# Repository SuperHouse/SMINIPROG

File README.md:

Sonoff Mini Programming Jig
===========================
Copyright 2019-2020 SuperHouse Automation Pty Ltd  www.superhouse.tv  

Pogo pin board for programming a Sonoff Mini using the test points on
its PCB.

Exposes the connections to an ESP-Prog header, which can be used for
discrete wire connections or to plug in an ESPFlasher programmer.

www.superhouse.tv/sminiprog

INSTALLATION
------------
The design is saved as an EAGLE project. EAGLE PCB design software is
available from www.cadsoftusa.com free for non-commercial use. To use
this project download it and place the directory containing these files
into the "eagle" directory on your computer. Then open EAGLE and
navigate to the project.

DISTRIBUTION
------------
The specific terms of distribution of this project are governed by the
license referenced below.

LICENSE
-------
Licensed under the TAPR Open Hardware License (www.tapr.org/OHL).
The "license" folder within this repository also contains a copy of
this license in plain text format.

CREDITS
-------
Designed by Jonathan Oxer (jon@oxer.com.au)

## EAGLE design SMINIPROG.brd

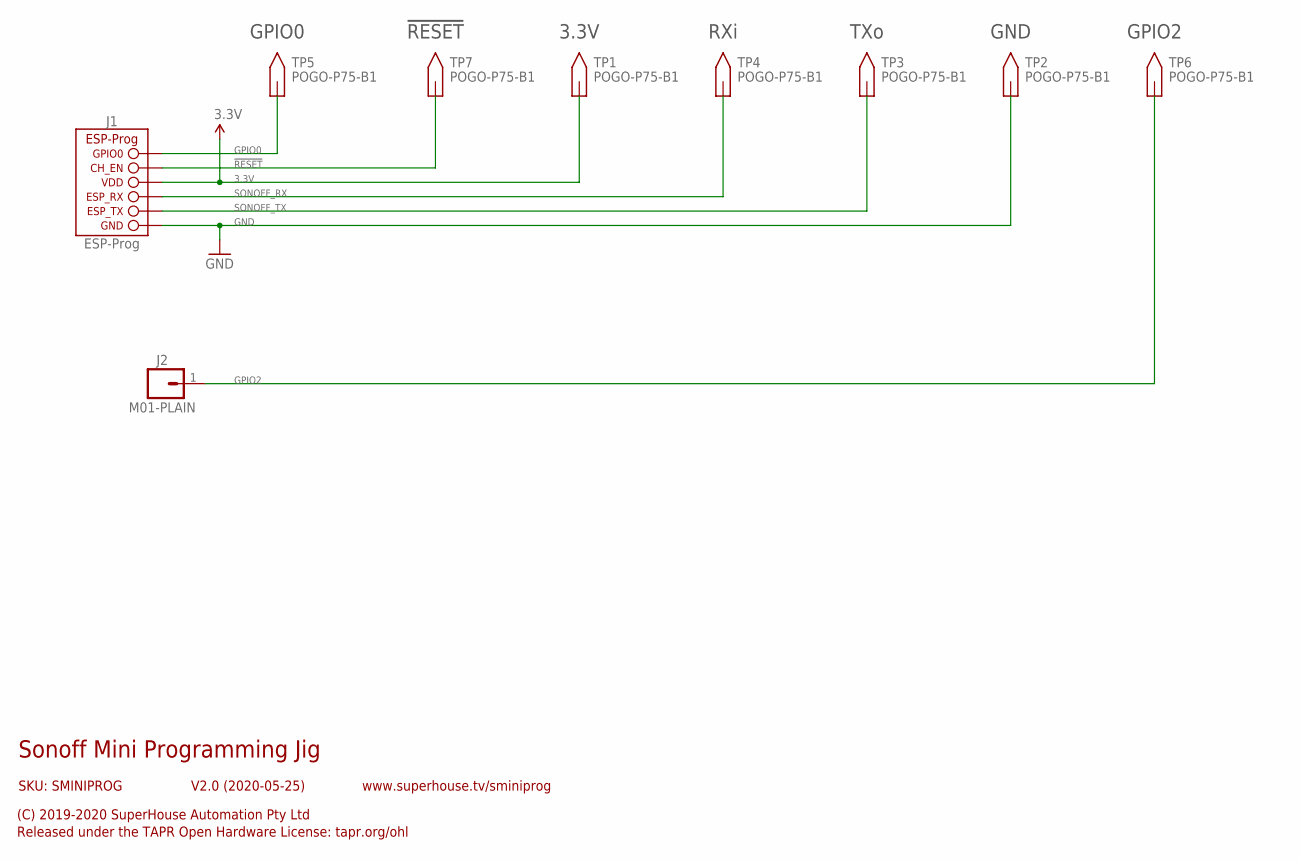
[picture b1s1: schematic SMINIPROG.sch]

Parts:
J1: ESP-PROG-1X6-2.54-SOCKET-RA; 1X6-2.54-SOCKET-RA
J2: M01-PLAIN; 1X01
TP1, TP2, TP3, TP4, TP5, TP6, TP7: POGO-P75-B1; PIN-1.02

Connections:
3.3V: J1.4 (VDD), TP1.P$1
!RESET: J1.5 (CH_EN), TP7.P$1
GND: J1.1 (GND), TP2.P$1
GPIO0: J1.6 (GPIO0), TP5.P$1
GPIO2: J2.1, TP6.P$1
SONOFF_RX: J1.3 (ESP_RX), TP4.P$1
SONOFF_TX: J1.2 (ESP_TX), TP3.P$1

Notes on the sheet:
Sonoff Mini Programming Jig
V2.0 (2020-05-25)
(C) 2019-2020 SuperHouse Automation Pty Ltd
Released under the TAPR Open Hardware License: tapr.org/ohl
www.superhouse.tv/sminiprog
SKU: SMINIPROG
3.3V
GND
TXo
RXi
GPIO0
GPIO2
!RESET

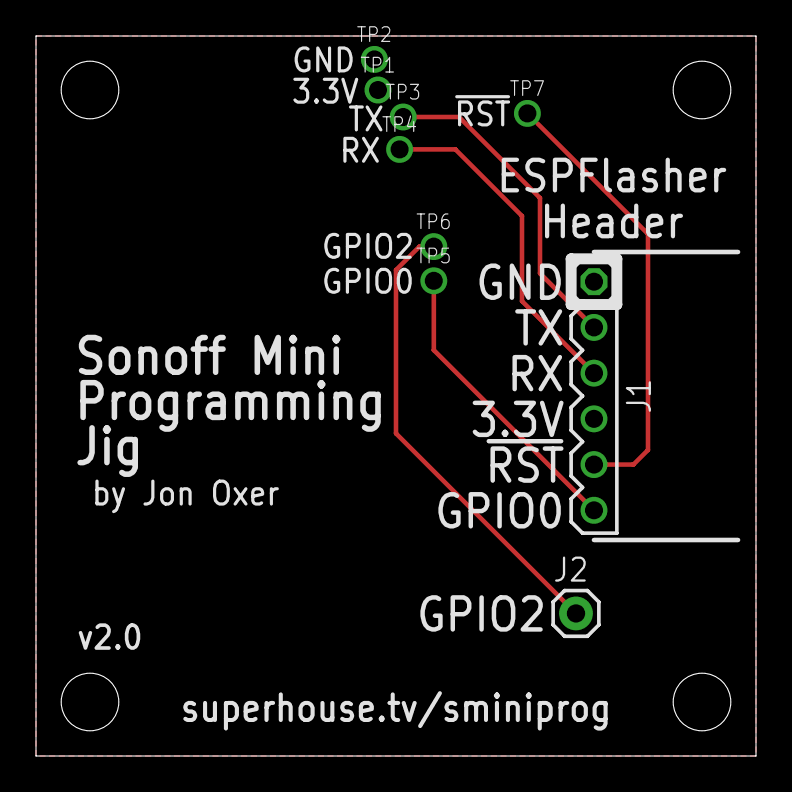
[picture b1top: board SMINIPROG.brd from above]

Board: 2 copper layers, 40.0 x 40.0 mm, 9 parts (0 on the bottom side), 7 nets.

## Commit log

2019-09-06 Initial project import
2019-09-07 Routing for v1.0 release
2019-09-07 Added render and updated README
2020-05-27 Replaced ESP-Prog header, major update for v2.0 release
2020-05-27 Updated docs and render for v2.0 release

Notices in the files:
SMINIPROG.brd:
Released under the terms of
the TAPR Open Hardware Licence:
tapr.org/OHL
